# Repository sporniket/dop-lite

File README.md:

# Sporniket's 'Delivery Of Power' lite

> [WARNING] Please read carefully this note before using this project. It contains important facts.

Content

1. What is **Sporniket's 'Delivery Of Power' lite**, and when to use it ?
2. What should you know before using **Sporniket's 'Delivery Of Power' lite** ?
3. How to use **Sporniket's 'Delivery Of Power' lite** ?
4. Known issues
5. Miscellanous

## 1. What is **Sporniket's 'Delivery Of Power' lite**, and when to use it ?

**Sporniket's 'Delivery Of Power' lite** is an experimental power adapter using USB-C Power Delivery limited to around 15W, with up to 0.5A for the 12V rail, and up to 3A for the 5V rail.

This is a project designed with [Kicad](https://www.kicad.org/).

### Licence

**Sporniket's 'Delivery Of Power' lite** is marked with CC0 1.0 Universal. To view a copy of this license, visit http://creativecommons.org/publicdomain/zero/1.0

**Sporniket's 'Delivery Of Power' lite** is distributed in the hope that it will be useful, but WITHOUT ANY WARRANTY; without even the implied warranty of MERCHANTABILITY or FITNESS FOR A PARTICULAR PURPOSE.

### Releases notes

> Nothing yet

## 2. What should you know before using **Sporniket's 'Delivery Of Power' lite** ?

So far, **Sporniket's 'Delivery Of Power' lite** has never been built. Thus it is not tested at all. It should work. Maybe. Or not. It should be safe. Maybe. Or not.

**Sporniket's 'Delivery Of Power' lite** is designed using [Kicad](https://www.kicad.org/).

The git repository use several submodules that one has to fetch in order to get the symbols, footprint and 3dmodels. One submodule requires [python3](https://www.python.org) and [GNU make](https://www.gnu.org/software/make/) to generate the libraries of symbols for integrated circuits.

> Do not use **Sporniket's 'Delivery Of Power' lite** if this project is not suitable for your project.

## 3. How to use **Sporniket's 'Delivery Of Power' lite** ?

### From sources

To get the latest available models, one must clone the git repository **and the submodules**. Then some modules needs a build step to generate its libraries.

	git clone --recurse-submodules https://github.com/sporniket/dop-lite.git
	cd dop-lite/kicad-symbols-generated
	make

Then, open the project in Kicad.

### From github releases

A github **schematic only** release (with `schematics` in the release tag and name) will provide a PDF of the schematics

A github **regular** release will provide :

* A standalone Kicad project (all custom libraries included and ready to use)
* A PDF of the schematics
* A PDF of the silkscreen
* If applicable, a Gerber for boardmanufacturer. Some details may have been adapted for a specific manufacturer.
* If applicable, a BOM, and pick an place files, likely for a specific manufacturer too.

## 4. Known issues
See the [project issues](https://github.com/sporniket/dop-lite/issues) page.

## 5. Miscellanous

### Report issues
Use the [project issues](https://github.com/sporniket/dop-lite/issues) page.

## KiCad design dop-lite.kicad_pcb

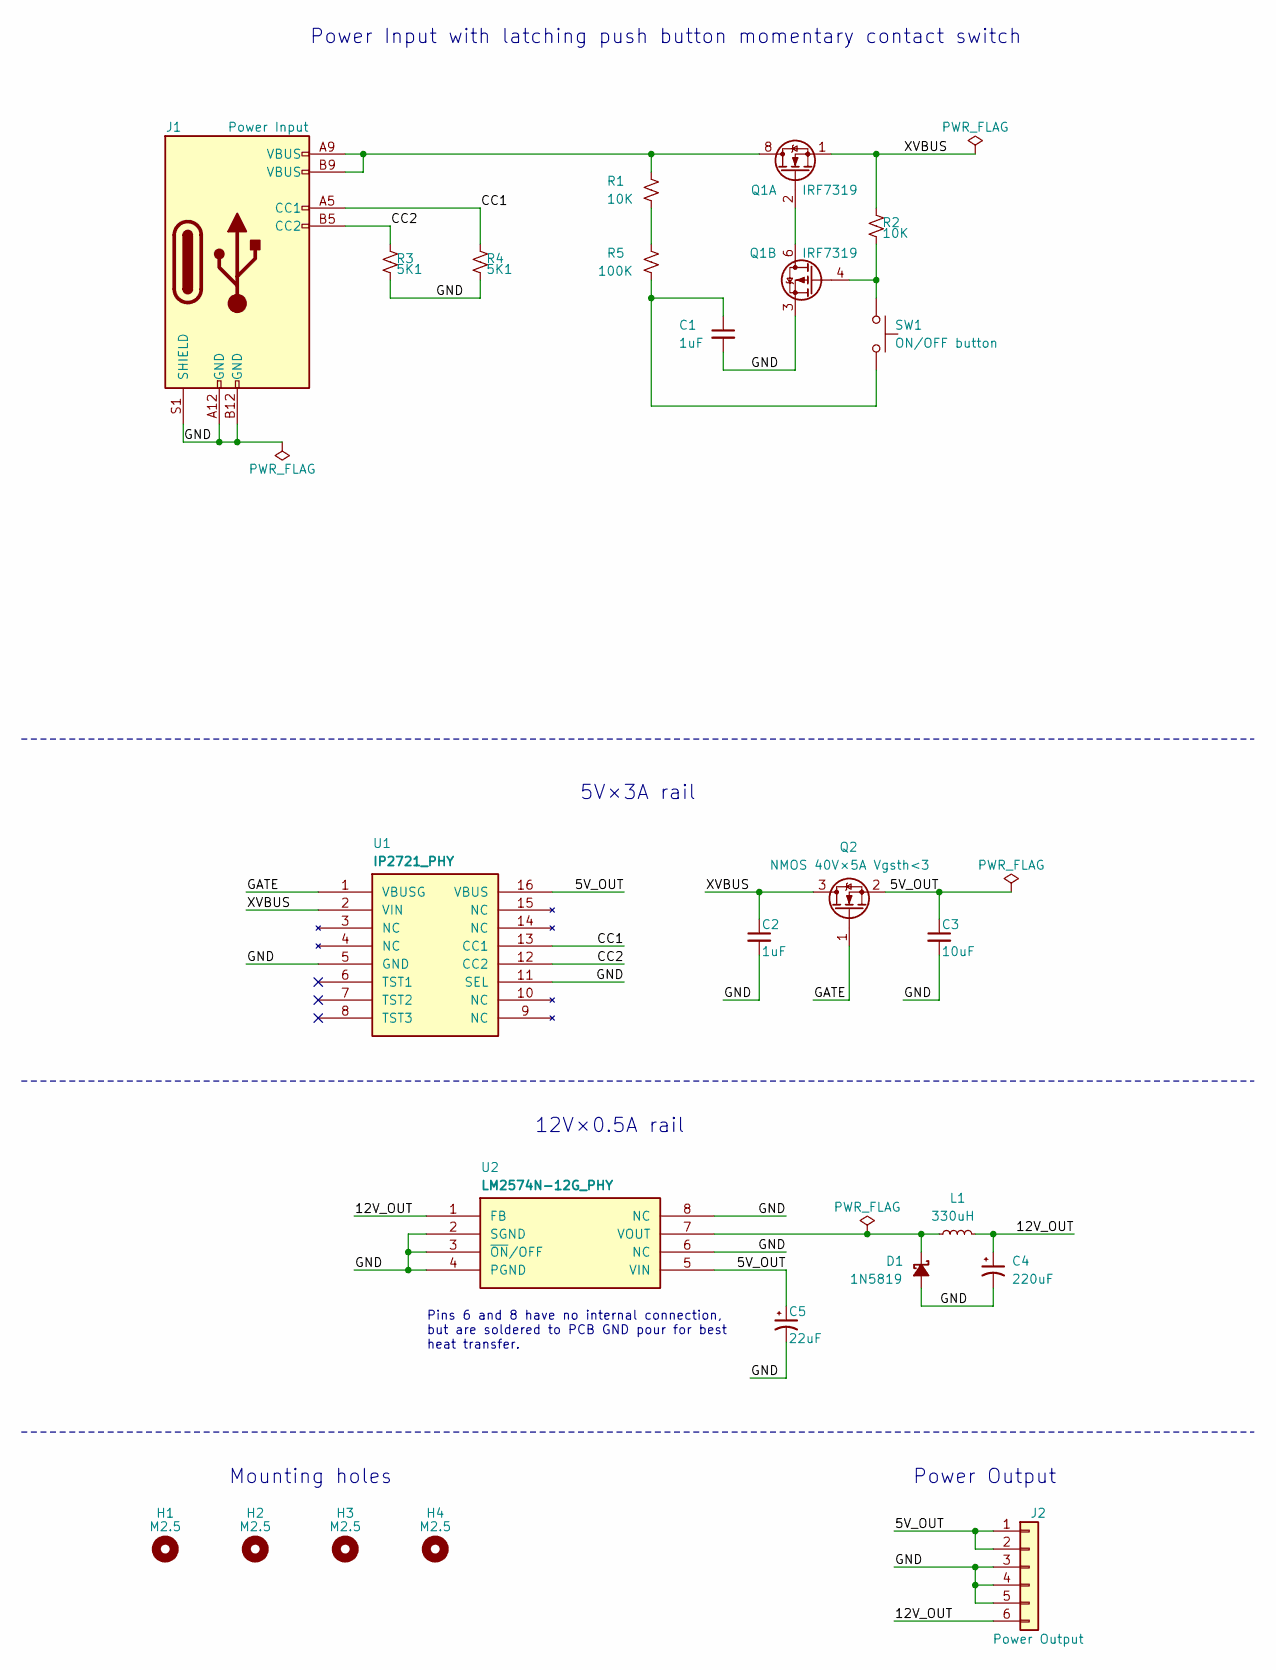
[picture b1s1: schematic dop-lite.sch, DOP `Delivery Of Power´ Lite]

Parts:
C1, C2: 1uF; C_0805_2012Metric_Pad1.18x1.45mm_HandSolder
C3: 10uF; C_0805_2012Metric_Pad1.18x1.45mm_HandSolder
C4: 220uF; CP_Radial_D8.0mm_P3.50mm
C5: 22uF; C_0805_2012Metric_Pad1.18x1.45mm_HandSolder
D1: 1N5819; D_SOD-123
H1, H2, H3, H4: M2.5; MountingHole_2.7mm_M2.5_Pad
J1: Power Input; USB_C_Receptacle_HRO_TYPE-C-31-M-17
J2: Power Output; PinHeader_1x06_P2.54mm_Vertical
L1: 330uH; L_12x12mm_H8mm_Coilcraft_MSS1278T
Q1: IRF7319; SOIC-8_3.9x4.9mm_P1.27mm
Q2: NMOS 40V×5A Vgsth<3; SOT-23
R1, R2: 10K; R_0805_2012Metric_Pad1.20x1.40mm_HandSolder
R3, R4: 5K1; R_0805_2012Metric_Pad1.20x1.40mm_HandSolder
R5: 100K; R_0805_2012Metric_Pad1.20x1.40mm_HandSolder
SW1: ON/OFF button; PinHeader_1x02_P2.54mm_Vertical
U1: IP2721_PHY; TSSOP-16_4.4x5mm_P0.65mm
U2: LM2574N−12G_PHY; DIP-8_W7.62mm_LongPads

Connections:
/5V_OUT: C3.1, C5.1, J2.1, J2.2, Q2.2 (S), U1.16 (VBUS), U2.5 (VIN)
/12V_OUT: C4.1, J2.6, L1.2, U2.1 (FB)
/CC1: J1.A5 (CC1), R4.1, U1.13 (CC1)
/CC2: J1.B5 (CC2), R3.1, U1.12 (CC2)
/GATE: Q2.1 (G), U1.1 (VBUSG)
/GND: C1.2, C2.2, C3.2, C4.2, C5.2, D1.2 (A), J1.A12 (GND), J1.B12 (GND), J1.S1 (SHIELD), J2.3, J2.4, J2.5, Q1.3 (1), R3.2, R4.2, U1.5 (GND), U1.11 (SEL), U2.2 (SGND), U2.3 (~ON~/OFF), U2.4 (PGND), U2.6 (NC), U2.8 (NC)
/XVBUS: C2.1, Q1.1 (S), Q2.3 (D), R2.1, U1.2 (VIN)
unnamed: C1.1, R5.2, SW1.2
unnamed: D1.1 (K), L1.1, U2.7 (VOUT)
unnamed: J1.A9 (VBUS), J1.B9 (VBUS), Q1.7 (D), Q1.8 (D), R1.1
unnamed: Q1.2 (G), Q1.5 (D), Q1.6 (D)
unnamed: Q1.4 (G), R2.2, SW1.1
unnamed: R1.2, R5.1

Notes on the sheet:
Power Input with latching push button momentary contact switch
5V×3A rail
12V×0.5A rail
Power Output
Pins 6 and 8 have no internal connection, but are soldered to PCB GND pour for best heat transfer.
Mounting holes

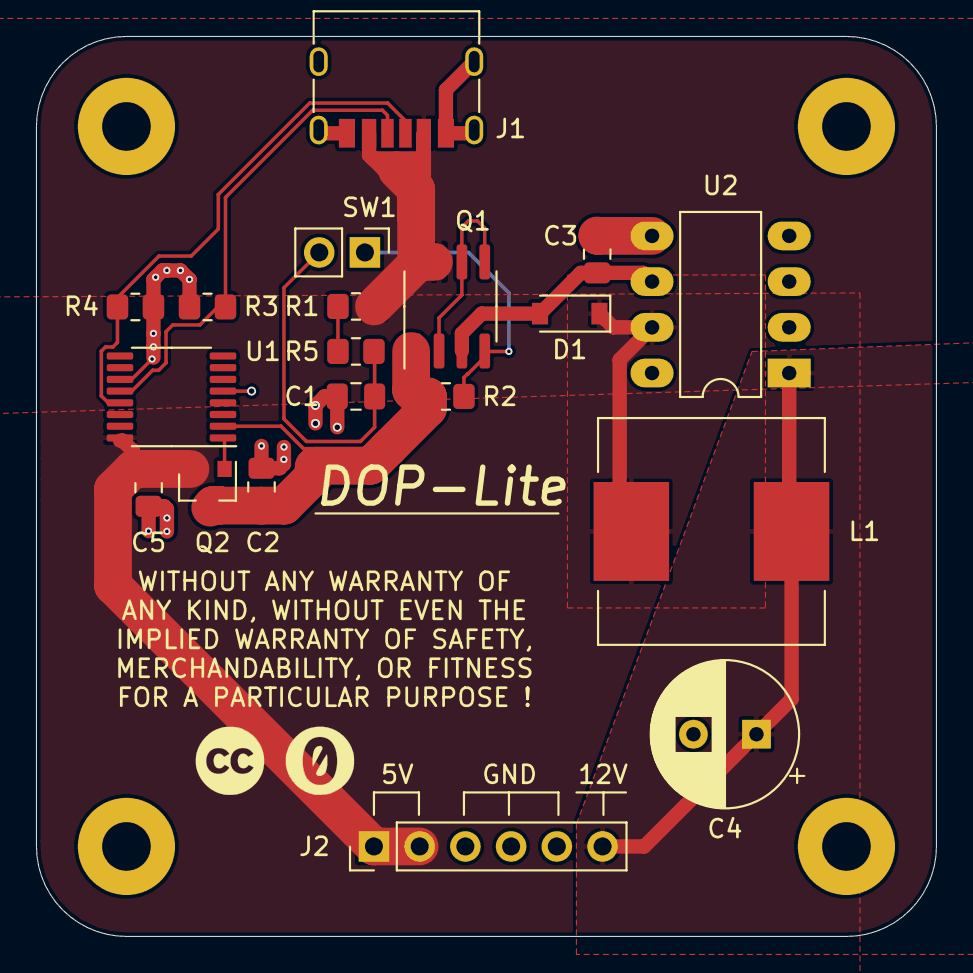
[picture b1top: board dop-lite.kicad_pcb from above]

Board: 4 copper layers, 50.0 x 50.0 mm, 23 parts (0 on the bottom side), 13 nets.

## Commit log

2022-06-10 update submodules
2022-06-10 added reference datasheets
2022-06-10 first completed draft
2022-06-10 Renumbering of components
2022-06-10 Conception rules
2022-06-10 fixed wrong use of vbus vs xvbus, finished pcb draft
2022-06-11 update symbols
2022-06-11 page description : the url of the source repository should be put as a sheet commentary
2022-06-11 fixed power sources, no more ERC
2022-06-11 decorate PCB (cc-0 logos, disclaimer, title)
2022-06-11 Prepare README before first public push
2022-06-11 use jpg format for gallery
2022-06-12 update a3 page design
2022-06-23 Resolves #1 : Use M2.5 mounting hole
2022-06-23 rotate pcb to be legible without bending the neck
2022-06-23 Resolves #2 : Move the usb receptacle 1~1.25 mm to the outer edge ; add some measurements
